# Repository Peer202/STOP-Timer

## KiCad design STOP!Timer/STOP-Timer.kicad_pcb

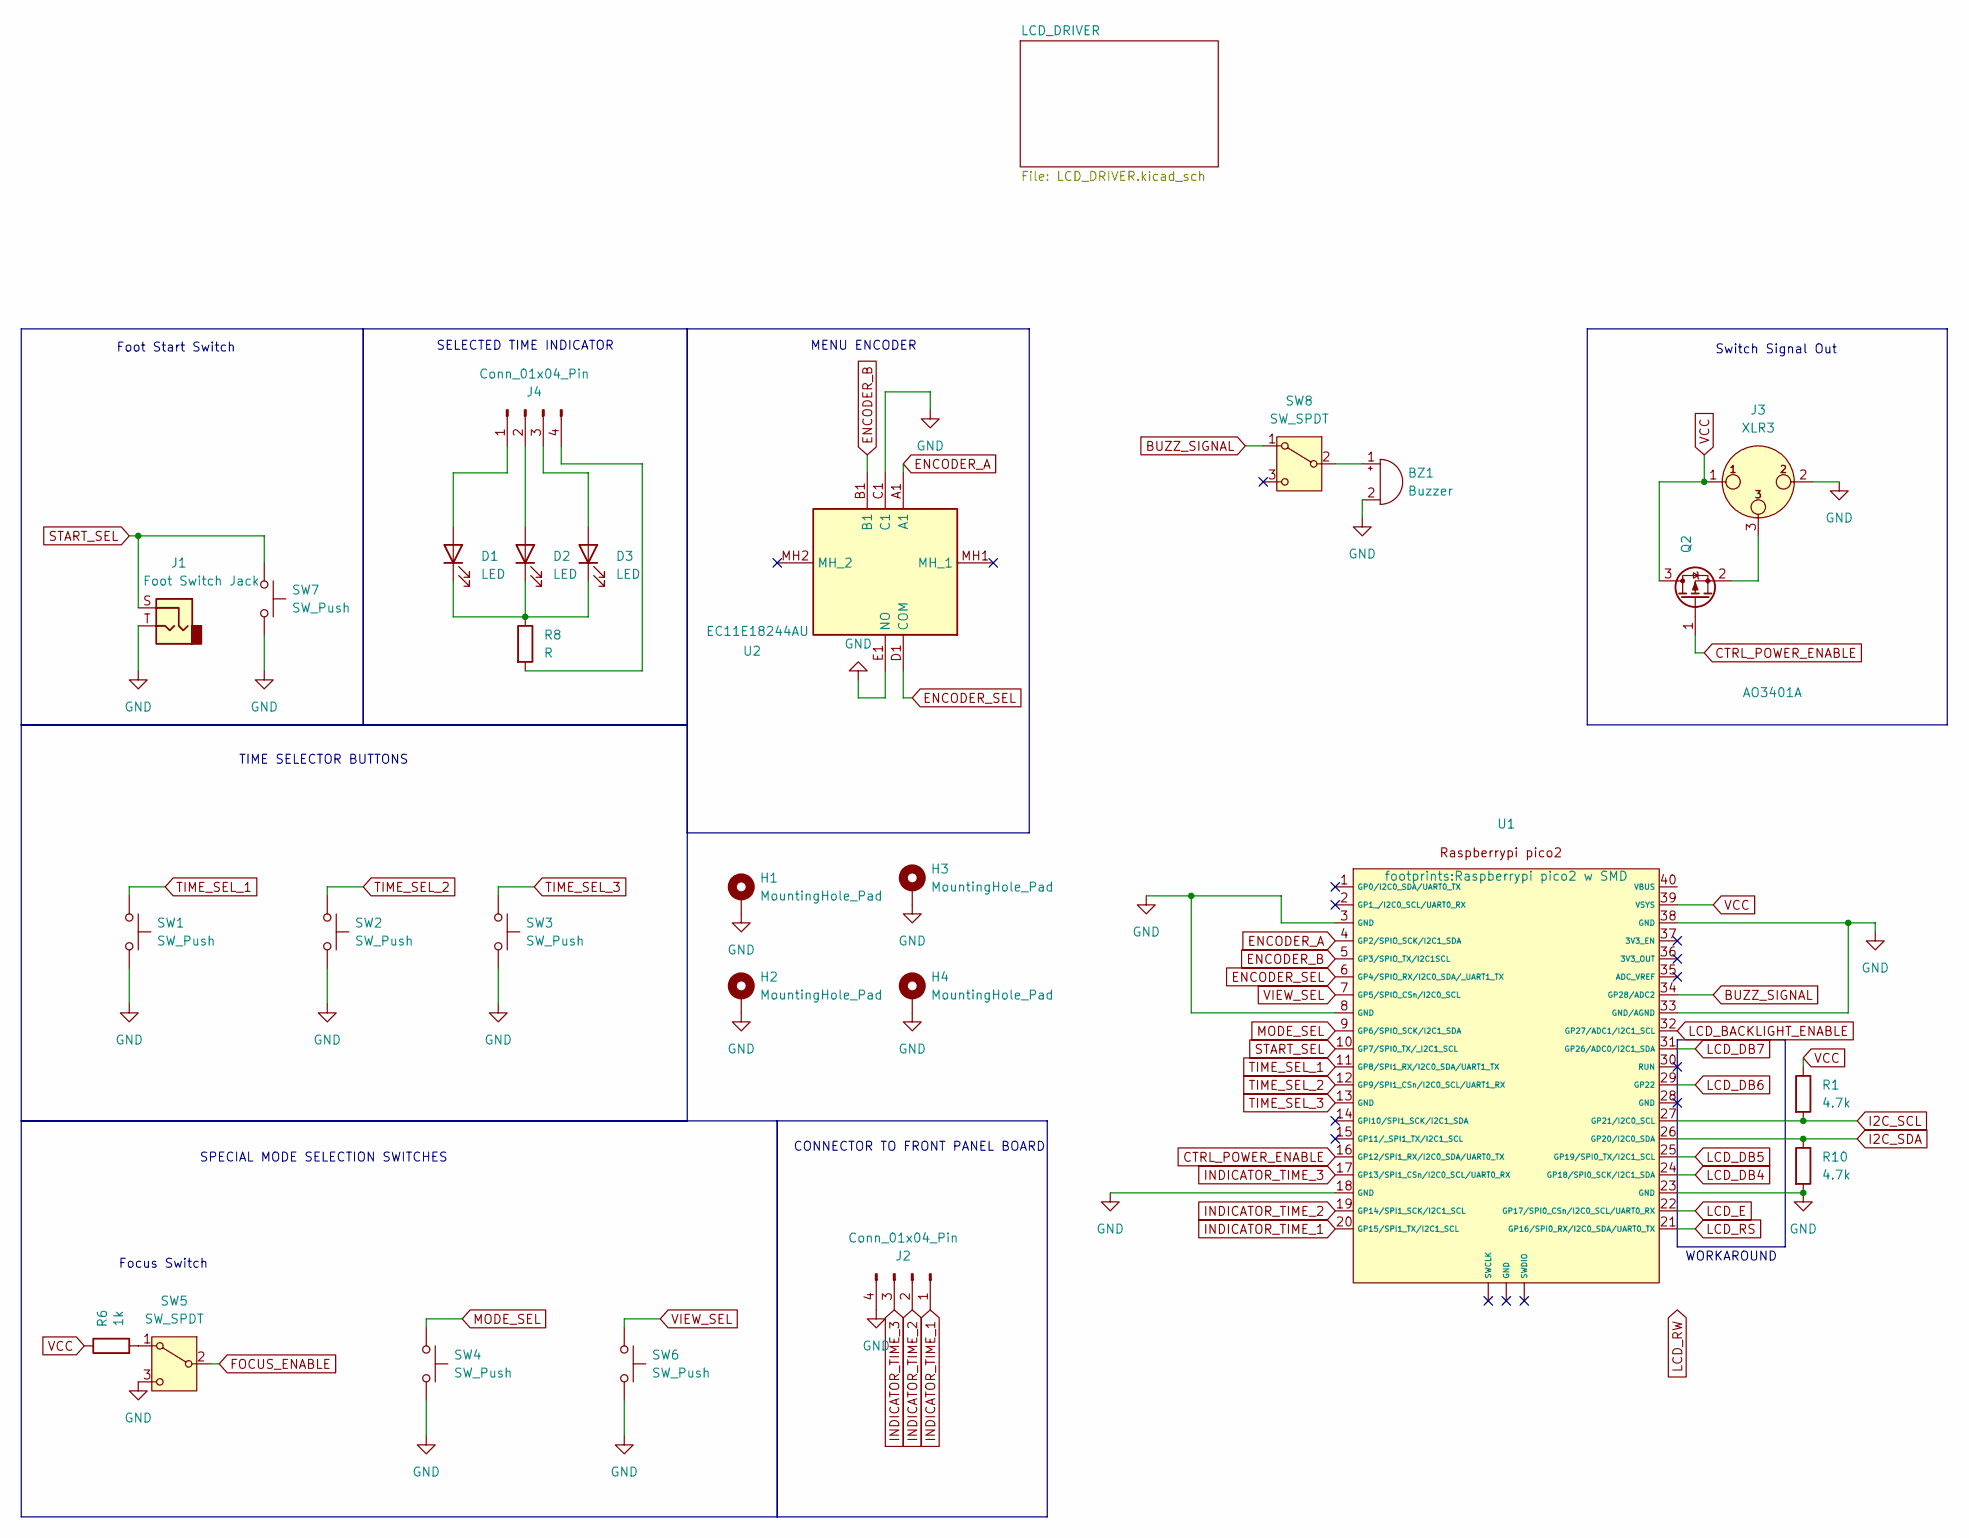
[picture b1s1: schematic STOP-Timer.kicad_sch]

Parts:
BZ1: Buzzer; Buzzer_12x9.5RM7.6; JLC C2877
D1, D2, D3: LED; LED_0805_2012Metric_Pad1.15x1.40mm_HandSolder
H1, H2, H3, H4: MountingHole_Pad; MountingHole_3.2mm_M3_DIN965_Pad
J1: Foot Switch Jack; NEUTRIK NMJ2HF-S
J2: Conn_01x04_Pin; PinHeader_1x04_P2.54mm_Vertical
J3: XLR3; Jack_XLR_Neutrik_NC3MAAH-0_Horizontal; JLC C368470
J4: Conn_01x04_Pin; PinSocket_1x04_P2.54mm_Vertical
Q2: AO3401A; SOT-23; JLC C15127
R1, R10: 4.7k; R_0805_2012Metric_Pad1.20x1.40mm_HandSolder; JLC C17673
R6: 1k; R_0805_2012Metric_Pad1.20x1.40mm_HandSolder; JLC C2907295
R8: R; R_0805_2012Metric_Pad1.20x1.40mm_HandSolder
SW1, SW2, SW3, SW4, SW6, SW7: SW_Push; SW_Cherry_MX_1.50u_PCB_3dmodel; JLC C49234237
SW5: SW_SPDT
SW8: SW_SPDT; SW_SPDT_PCM12; JLC C221841
U1: Raspberrypi pico2 w SMD; JLC C41407547
U2: EC11E18244AU; Mouser Part Number 688-EC11E18244AU

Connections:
BUZZ_SIGNAL: SW8.1 (A), U1.34 (GP28/ADC2)
CTRL_POWER_ENABLE: Q2.1 (G), U1.16 (GP12/SPI1_RX/I2C0_SDA/UART0_TX)
ENCODER_A: U1.4 (GP2/SPIO_SCK/I2C1_SDA), U2.A1
ENCODER_B: U1.5 (GP3/SPIO_TX/I2C1SCL), U2.B1
ENCODER_SEL: U1.6 (GP4/SPIO_RX/I2C0_SDA/_UART1_TX), U2.D1 (COM)
GND: BZ1.2 (-), H1.1, H2.1, H3.1, H4.1, J1.T, J2.4, J3.2, R10.2, SW1.2, SW2.2, SW3.2, SW4.2, SW5.3 (C), SW6.2, SW7.2, U1.3 (GND), U1.8 (GND), U1.18 (GND), U1.23 (GND), U1.33 (GND/AGND), U1.38 (GND), U2.C1, U2.E1 (NO); also elsewhere on the board
I2C_SCL: R1.2, U1.27 (GP21/I2C0_SCL); also elsewhere on the board
I2C_SDA: R10.1, U1.26 (GP20/I2C0_SDA); also elsewhere on the board
INDICATOR_TIME_1: J2.1, U1.20 (GP15/SPI1_TX/I2C1_SCL)
INDICATOR_TIME_2: J2.2, U1.19 (GP14/SPI1_SCK/I2C1_SCL)
INDICATOR_TIME_3: J2.3, U1.17 (GP13/SPI1_CSn/I2C0_SCL/UART0_RX)
LCD_BACKLIGHT_ENABLE: U1.32 (GP27/ADC1/I2C1_SCL); also elsewhere on the board
LCD_DB4: U1.24 (GP18/SPI0_SCK/I2C1_SDA); also elsewhere on the board
LCD_DB5: U1.25 (GP19/SPI0_TX/I2C1_SCL); also elsewhere on the board
LCD_DB6: U1.29 (GP22); also elsewhere on the board
LCD_DB7: U1.31 (GP26/ADC0/I2C1_SDA); also elsewhere on the board
LCD_E: U1.22 (GP17/SPI0_CSn/I2C0_SCL/UART0_RX); also elsewhere on the board
LCD_RS: U1.21 (GP16/SPI0_RX/I2C0_SDA/UART0_TX); also elsewhere on the board
MODE_SEL: SW4.1, U1.9 (GP6/SPIO_SCK/I2C1_SDA)
unnamed: BZ1.1 (+), SW8.2 (B)
unnamed: D1.2 (A), J4.1
unnamed: D1.1 (K), D2.1 (K), D3.1 (K), R8.1
unnamed: D2.2 (A), J4.2
unnamed: D3.2 (A), J4.3
unnamed: J4.4, R8.2
unnamed: J3.3, Q2.2 (S)
unnamed: R6.2, SW5.1 (A)
START_SEL: J1.S, SW7.1, U1.10 (GP7/SPI0_TX/_I2C1_SCL)
TIME_SEL_1: SW1.1, U1.11 (GP8/SPI1_RX/I2C0_SDA/UART1_TX)
TIME_SEL_2: SW2.1, U1.12 (GP9/SPI1_CSn/I2C0_SCL/UART1_RX)
TIME_SEL_3: SW3.1, U1.13 (GND)
VCC: J3.1, Q2.3 (D), R1.1, R6.1, U1.39 (VSYS); also elsewhere on the board
VIEW_SEL: SW6.1, U1.7 (GP5/SPIO_CSn/I2C0_SCL)

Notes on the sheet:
MENU ENCODER
SELECTED TIME INDICATOR
TIME SELECTOR BUTTONS
Switch Signal Out
WORKAROUND
SPECIAL MODE SELECTION SWITCHES
CONNECTOR TO FRONT PANEL BOARD
Foot Start Switch
Focus Switch

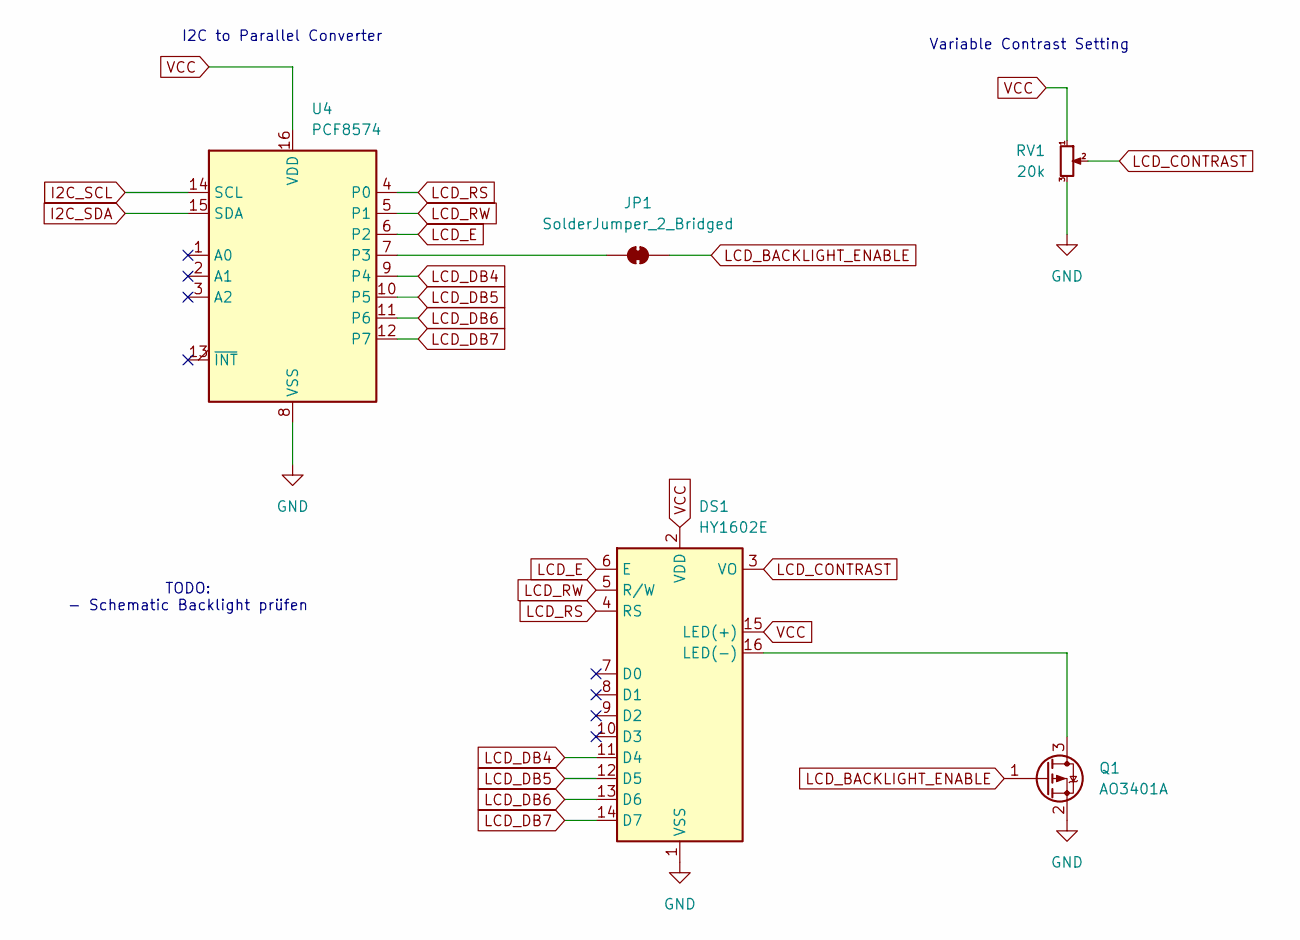
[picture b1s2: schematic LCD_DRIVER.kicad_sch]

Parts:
DS1: HY1602E; WC1602A
JP1: SolderJumper_2_Bridged; SolderJumper-2_P1.3mm_Bridged_Pad1.0x1.5mm
Q1: AO3401A; SOT-23; JLC C15127
RV1: 20k; Potentiometer_Bourns_3386W_Horizontal; JLC C221841
U4: PCF8574; SSOP-20_4.4x6.5mm_P0.65mm; JLC C57790

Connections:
GND: DS1.1 (VSS), Q1.2 (S), RV1.3, U4.8 (VSS); also elsewhere on the board
I2C_SCL: U4.14 (SCL); also elsewhere on the board
I2C_SDA: U4.15 (SDA); also elsewhere on the board
LCD_BACKLIGHT_ENABLE: JP1.1 (A), Q1.1 (G); also elsewhere on the board
LCD_CONTRAST: DS1.3 (VO), RV1.2
LCD_DB4: DS1.11 (D4), U4.9 (P4); also elsewhere on the board
LCD_DB5: DS1.12 (D5), U4.10 (P5); also elsewhere on the board
LCD_DB6: DS1.13 (D6), U4.11 (P6); also elsewhere on the board
LCD_DB7: DS1.14 (D7), U4.12 (P7); also elsewhere on the board
LCD_E: DS1.6 (E), U4.6 (P2); also elsewhere on the board
LCD_RS: DS1.4 (RS), U4.4 (P0); also elsewhere on the board
LCD_RW: DS1.5 (R/W), U4.5 (P1)
unnamed: DS1.16 (LED(-)), Q1.3 (D)
unnamed: JP1.2 (B), U4.7 (P3)
VCC: DS1.2 (VDD), DS1.15 (LED(+)), RV1.1, U4.16 (VDD); also elsewhere on the board

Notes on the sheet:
TODO: - Schematic Backlight prüfen
Variable Contrast Setting
I2C to Parallel Converter

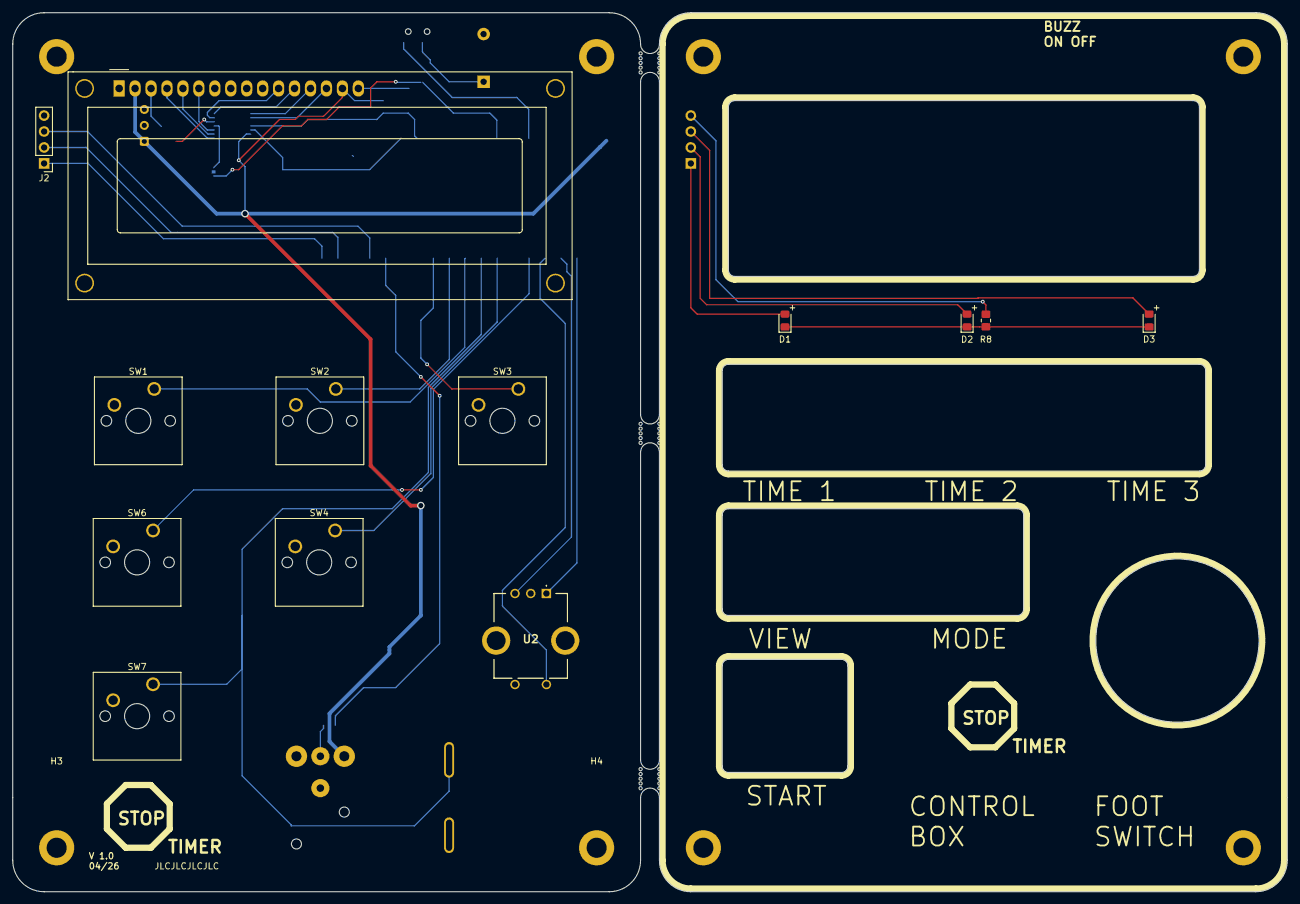
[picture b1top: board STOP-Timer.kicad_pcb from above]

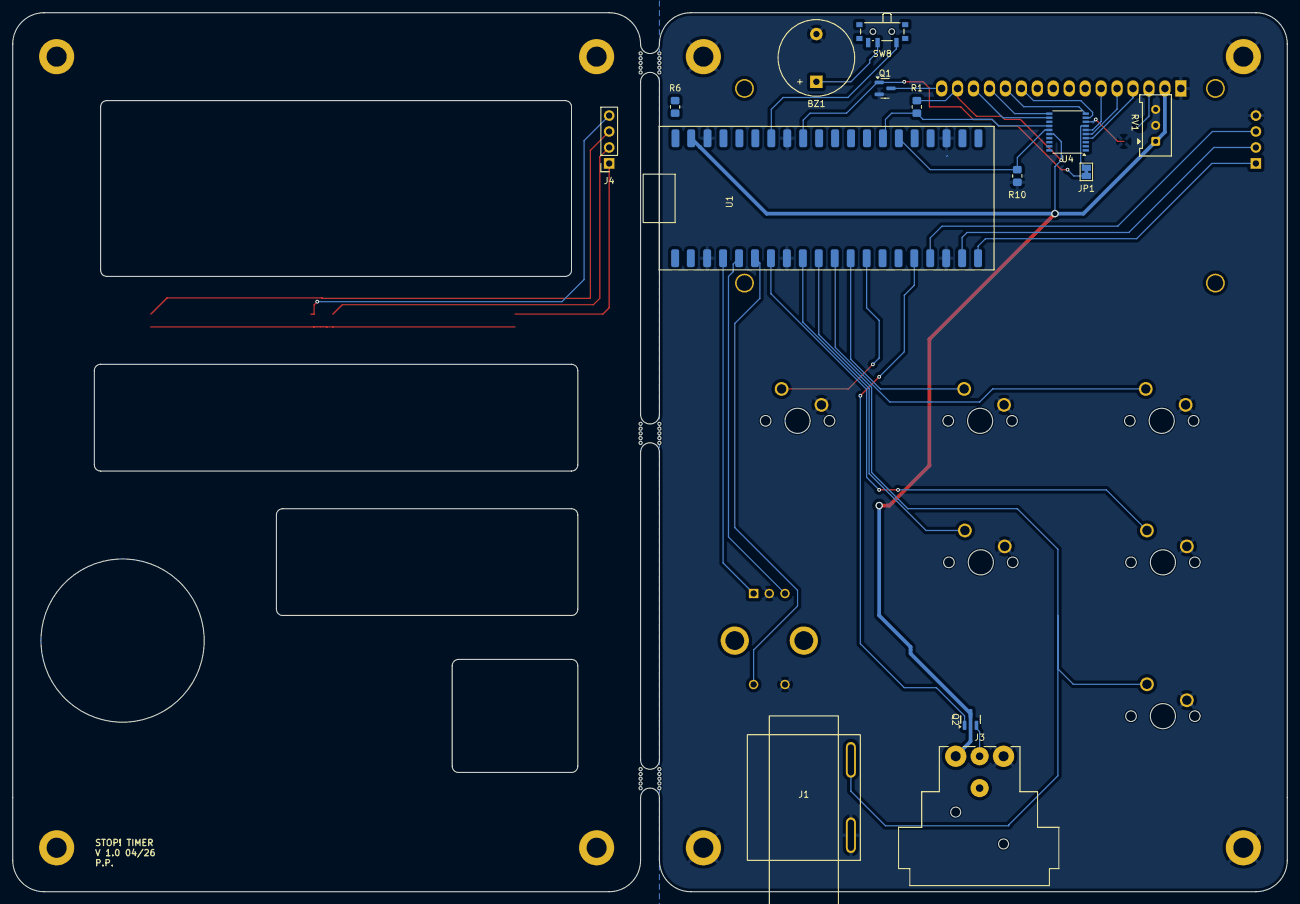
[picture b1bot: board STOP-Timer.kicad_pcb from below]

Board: 2 copper layers, 203.0 x 140.0 mm, 34 parts (14 on the bottom side), 36 nets.

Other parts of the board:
mouse-bite-3mm-slot, mouse-bite-3mm-slot#2, mouse-bite-3mm-slot#3: VAL**; mouse-bite-3mm-slot

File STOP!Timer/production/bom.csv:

Designator,Footprint,Quantity,Value,LCSC Part #
"_4, _3, _2, ",,4,,
BZ1,Buzzer_12x9.5RM7.6,1,Buzzer,
"D1, D2, D3",0805,3,LED,
DS1,WC1602A,1,HY1602E,
J1,NEUTRIK NMJ2HF-S,1,Foot Switch Jack,
J2,PinHeader_1x04_P2.54mm_Vertical,1,Conn_01x04_Pin,
J3,Jack_XLR_Neutrik_NC3MAAH-0_Horizontal,1,XLR3,
J4,PinSocket_1x04_P2.54mm_Vertical,1,Conn_01x04_Pin,
"MOUSE-BITE-3MM-SLOT_3, MOUSE-BITE-3MM-SLOT_2, MOUSE-BITE-3MM-SLOT",mouse-bite-3mm-slot,3,VAL**,
"Q1, Q2",SOT-23,2,AO3401A,C15127
"R1, R10",0805,2,4.7k,
R6,0805,1,1k,
R8,0805,1,R,
RV1,Potentiometer_Bourns_3386P_Vertical,1, 20k,
"SW1, SW2, SW3, SW4, SW6, SW7",SW_Cherry_MX_1.50u_PCB_3dmodel,6,SW_Push,C49234237
SW8,SW_SPDT_PCM12,1,SW_SPDT,C221841
U1,Raspberrypi pico2 w SMD,1,~,
U2,EC11E18244AU,1,EC11E18244AU,
U4,SSOP-20_4.4x6.5mm_P0.65mm,1,PCF8574,C57790

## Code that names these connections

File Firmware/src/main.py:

#imports

import time
import machine
from machine import Pin
from lcd1602 import LCD1602
from menu.holder import MenuHolder
from menu.running import EnlargerRunningPage

from rotary_irq_rp2 import RotaryIRQ
#CONSTANTS
UPDATE_RATE = 5 # Hz
DELAY_BETWEEN_FRAMES = 1/UPDATE_RATE #s
DEBOUNCE_DURATION = 1 #s

# State Variables
Command_queue = []
times = [0,0,0]
times_selected = 0
encoder_last_value = 0
isr_last_time = 0
# PIN Definitions

# INPUTS

PIN_SWITCH_START = Pin(7,Pin.IN,Pin.PULL_UP)
PIN_SWITCH_MODE = Pin(6,Pin.IN,Pin.PULL_UP)
PIN_SWITCH_VIEW = Pin(5,Pin.IN,Pin.PULL_UP)

PIN_SWITCH_TIME_1 = Pin(8,Pin.IN,Pin.PULL_UP)
PIN_SWITCH_TIME_2 = Pin(9,Pin.IN,Pin.PULL_UP)
#PIN_SWITCH_TIME_3 = Pin(10,Pin.IN,Pin.PULL_UP)

PIN_SWITCH_ENCODER_SELECT = Pin(4,Pin.IN,Pin.PULL_UP)
#PIN_SWITCH_ENCODER_A = Pin(2,Pin.IN,Pin.PULL_UP)
#PIN_SWITCH_ENCODER_B = Pin(3,Pin.IN,Pin.PULL_UP)

# OUTPUTS
PIN_INDICATOR_TIME_1 = Pin(15,Pin.OUT)
PIN_INDICATOR_TIME_2 = Pin(14,Pin.OUT)
PIN_INDICATOR_TIME_3 = Pin(13,Pin.OUT)

PIN_BACKLIGHT_ENABLE = Pin(27,Pin.OUT)

PIN_CTRL_POWER_ENABLE = Pin(12,Pin.OUT)

LED_PINS = [PIN_INDICATOR_TIME_1,PIN_INDICATOR_TIME_2,PIN_INDICATOR_TIME_3]

class HardwareInterface():
    def __init__(self):
        self.lcd = LCD1602.begin_4bit(rs=16, e=17, db_7_to_4=[26, 22, 19, 18])
        self.enlarger_on = False

    def pass_menu(self,menu_object):
        self.menu = menu_object

    def on_for_sec(self,on_duration):
        self.switch_on()
        time.sleep(on_duration)
        self.switch_off()

    def switch_on(self):
        #print("Enlarger On")
        PIN_CTRL_POWER_ENABLE.on()
        self.enlarger_on = True
        self.toggle_all_leds()
    
    def switch_off(self):
        #print("Enlarger off")
        PIN_CTRL_POWER_ENABLE.off()
        self.enlarger_on = False
        self.toggle_all_leds()

    def print_to_disp(self,row,row_text):
        self.lcd.write_text(0, row, row_text)

    def clear_disp(self):
        self.lcd.clear()    

    def on_time_select(self,pin):
        if(pin == PIN_SWITCH_TIME_1):
           t = 0
        if(pin == PIN_SWITCH_TIME_2):
           t = 1
        #if(pin == PIN_SWITCH_TIME_3):
        #   t = 2
        self.menu.on_time_select(t)

    def toggle_all_leds(self):
        for pin in LED_PINS:
            pin.toggle()

    def led_all_off(self):
        for pin in LED_PINS:
            pin.off()

    def led_index_on(self,led_index):
        LED_PINS[led_index].on()

    def led_index_off(self,led_index):
        LED_PINS[led_index].off()


def InputISR(pin):
    global isr_last_time
    if(time.time() >= (isr_last_time + DEBOUNCE_DURATION)):
        if(len(Command_queue)==0):
            Command_queue.append(pin)
            print("ISR PIN: " + str(pin))
        isr_last_time = time.time()
    
def Execute_from_Queue():
    global Command_queue
    if(len(Command_queue)==0):
        return
    
    #state =  machine.disable_irq()
    irq_source = Command_queue[0]

    #menu.debug_print(irq_source)
    if(irq_source == PIN_SWITCH_MODE):
        menu.on_mode()

    if(irq_source == PIN_SWITCH_VIEW):
        menu.on_view()

    if(irq_source == PIN_SWITCH_ENCODER_SELECT):
        menu.on_select()
    if(irq_source == PIN_SWITCH_START):
        menu.on_start()

    Command_queue = []
    #machine.enable_irq(state=state)

def InputEncoder():
    global encoder_last_value
    _curr_value = encoder.value()
    #print(_curr_value)
    if(_curr_value > encoder_last_value):
        menu.on_increment()
        #print("Increment")
    if(_curr_value < encoder_last_value):
        menu.on_decrement()
        #print("decrement")
    else:
        #print("Encoder intterupt, but Value has not changed")
        pass
    encoder_last_value = _curr_value

    
hardware = HardwareInterface()
menu = MenuHolder(hardware_object=hardware,debug=True)

encoder = RotaryIRQ(
    pin_num_clk=2,
    pin_num_dt=3,
    min_val=0,
    max_val=10,
    incr=1,
    reverse=True,
    range_mode=RotaryIRQ.RANGE_UNBOUNDED,
    pull_up=True
)
encoder.add_listener(InputEncoder)

# INPUT INTERRUPTS

#PIN_SWITCH_START.irq(trigger=Pin.IRQ_FALLING, handler=hardware.on_start)
#PIN_SWITCH_MODE.irq(trigger=Pin.IRQ_FALLING, handler=hardware.on_mode)
#PIN_SWITCH_VIEW.irq(trigger=Pin.IRQ_FALLING, handler=hardware.on_view)
#PIN_SWITCH_ENCODER_SELECT.irq(trigger=Pin.IRQ_FALLING, handler=hardware.on_select)

for pin in [PIN_SWITCH_START,PIN_SWITCH_MODE,PIN_SWITCH_VIEW,PIN_SWITCH_ENCODER_SELECT]:
    pin.irq(trigger=Pin.IRQ_FALLING, handler=InputISR)

for pin in [PIN_SWITCH_TIME_1,PIN_SWITCH_TIME_2]: #,PIN_SWITCH_TIME_3]
    pin.irq(trigger=Pin.IRQ_FALLING, handler=hardware.on_time_select)

PIN_CTRL_POWER_ENABLE.off()
hardware.led_all_off()

PIN_BACKLIGHT_ENABLE.on()

time.sleep(0.1) # Wait for USB to become ready


#print("Hello, Pi Pico W!")

#menu.force_new_menu_layer(EnlargerRunningPage(menu,10))

while(True):
    #print(Command_queue)
    Execute_from_Queue()
    #PIN_BACKLIGHT_ENABLE.toggle()
    time.sleep(DELAY_BETWEEN_FRAMES)
    #time.sleep(2)
    #hardware.on_for_sec(5)
    menu.update_screen()

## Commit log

2026-01-20 Add .gitignore
2026-01-21 Remove Backup
2026-01-21 Move Symbols to lib subfolder
2026-01-21 Add LCD Circuit
2026-01-22 add rp2350 datasheet
2026-01-22 Add Encoder Schematic
2026-01-22 Add LCD Driver Schematic
2026-01-22 Move Schematics to seperate sheets + add some Pull Up Resistors
2026-03-25 Modify Library
2026-03-25 Update Schematic
2026-03-31 Update 31 03 2026
2026-03-31 Change Look of Board
2026-04-20 Initial Firmware Setup + Simulation
2026-04-22 gitignore update
2026-04-22 update Simulation config
2026-04-22 Update On Hardware Firmware
2026-04-22 Add Desktop_main .py for menu development and add first version of menu system
2026-05-09 Add flying Wire Display Connection Workaround
2026-05-10 First working Display and hardeware interface
2026-05-19 update 16.5.
2026-05-30 Update fter First Use
2026-06-06 Add FstopTestMode
